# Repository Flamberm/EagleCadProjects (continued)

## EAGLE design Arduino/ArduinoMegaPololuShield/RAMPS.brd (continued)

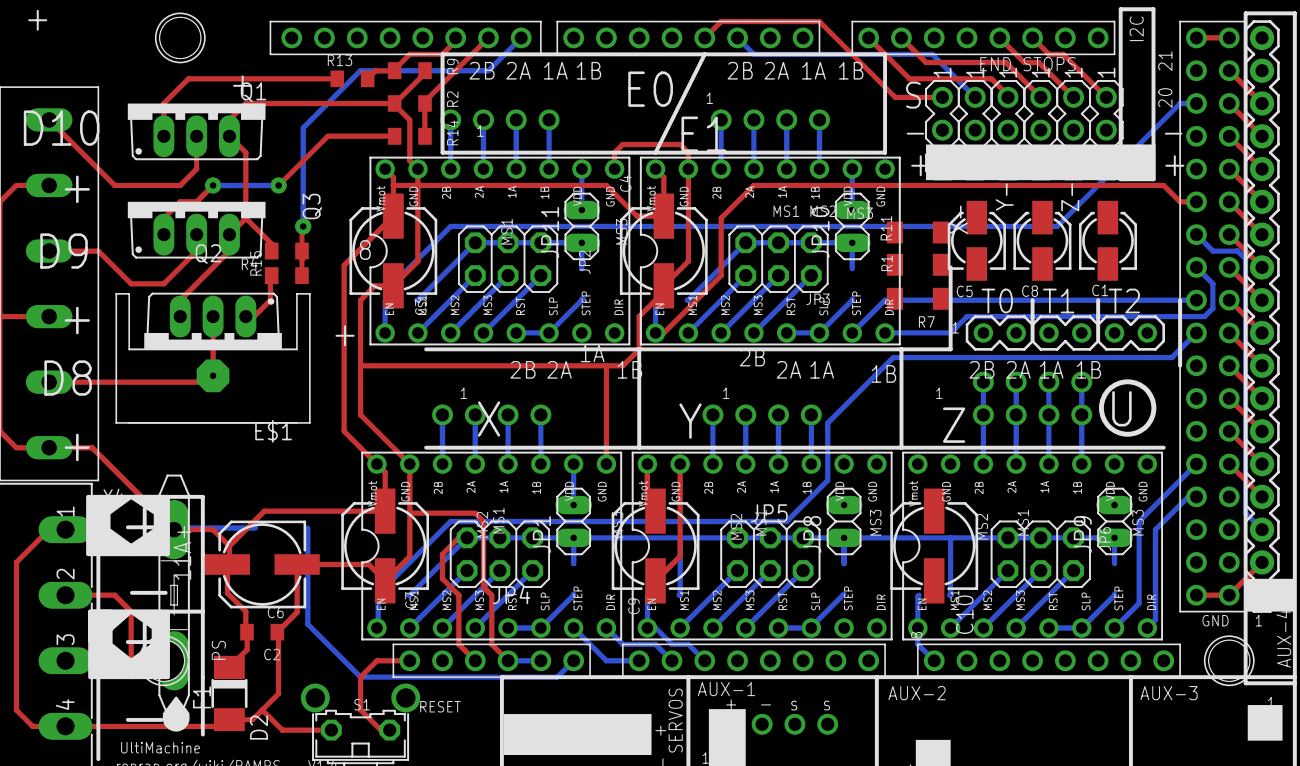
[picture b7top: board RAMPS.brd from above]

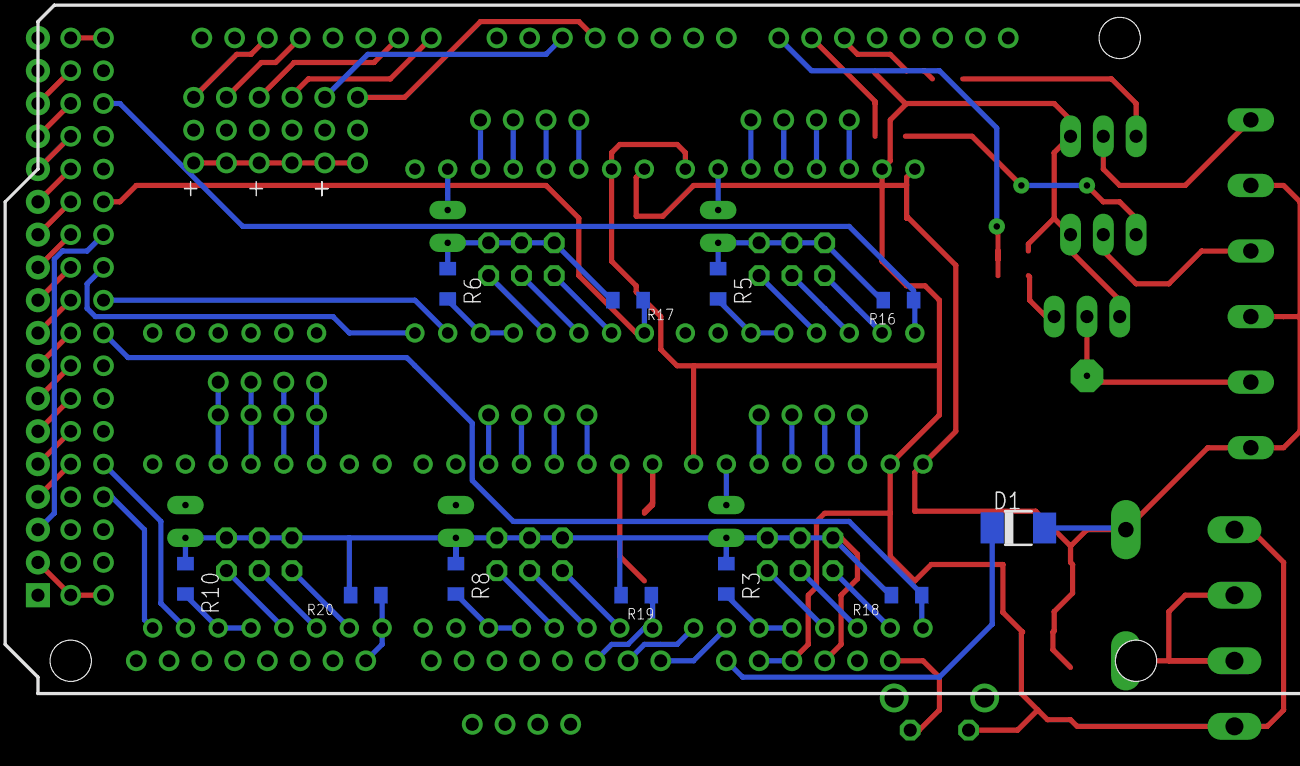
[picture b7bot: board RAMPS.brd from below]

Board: 2 copper layers, 70 parts (12 on the bottom side), 102 nets.

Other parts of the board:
E$1: SK95-3M3
